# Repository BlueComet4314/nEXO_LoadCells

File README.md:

# nEXO_LoadCells
Schematics for LoadCell Level Sensor work

## Schematic of PT100 circuit: 

## PCB Layout Vers. 02:

Parts:

| L0C | Part - Desc. | Digikey PIN |
| -- | -- | -- |
|C1| CAP_THT-0.1uF - 2.50mm | 2368-89410-ND |
|C2| CAP_SMD-47pF - 1.4mm | 490-6129-2-ND |
|C3| CAP_SMD-22pF - 1.4mm | 490-1253-2-ND |
|C6| CAP_SMD-68pF - 1.4mm | 490-11338-2-ND |
|J1| Conn-01x02_Male - 2.54mm | 77311-402-02LF-ND |
|J2| Conn-01x04_Female -2.54mm | 609-3920-ND |
|J3/J5| Load Cell Amp - HX711 | 1568-1436-ND |
| J4 & J6-10 | Conn header Vert-4POS - 2.54 mm | WM4826-ND|
|MCU1| Teensy 4.1 | 1568-DEV-16771-ND |
|P2| Arduino socket strip - Analog 01x08| 732-2859-ND |
|P4| Arduino socket strip - Power 01x08 | 732-2859-ND |
|P5| Arduino socket strip - PWM-01x10| S7008-ND |
|P6| Arduino socket strip - PWM-01x08 | 732-2859-ND |
|P8-P13| Arduino CONN 01X01 | SAM1122-01-ND |
|R2-R4| Resistor_SMD-10K | 2997-CR20103JTR-ND |
|R5| Resistor_SMD - 82k | 2997-CR20823JTR-ND |
|R6| Resistor_SMD - 39k | 2997-CR20393JTR-ND |
|Teensy_Ethernet1| Teensy Ethernet 1P | 1278-1052-ND |
|U1| MSOP-10P| 505-AD7151BRMZ-ND |

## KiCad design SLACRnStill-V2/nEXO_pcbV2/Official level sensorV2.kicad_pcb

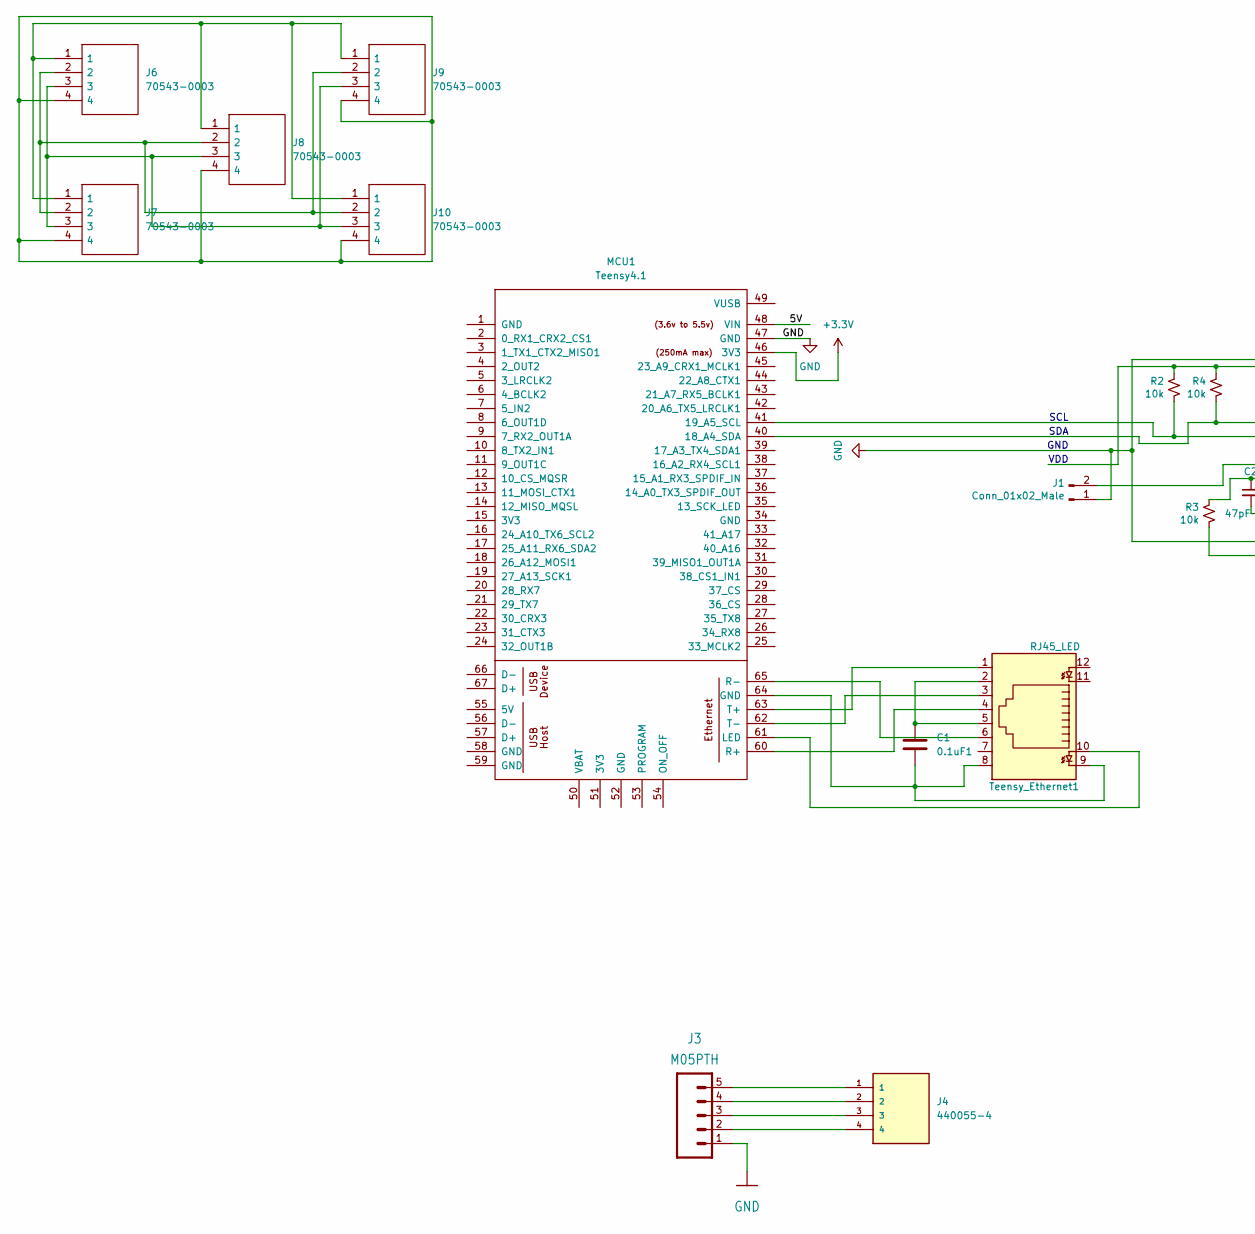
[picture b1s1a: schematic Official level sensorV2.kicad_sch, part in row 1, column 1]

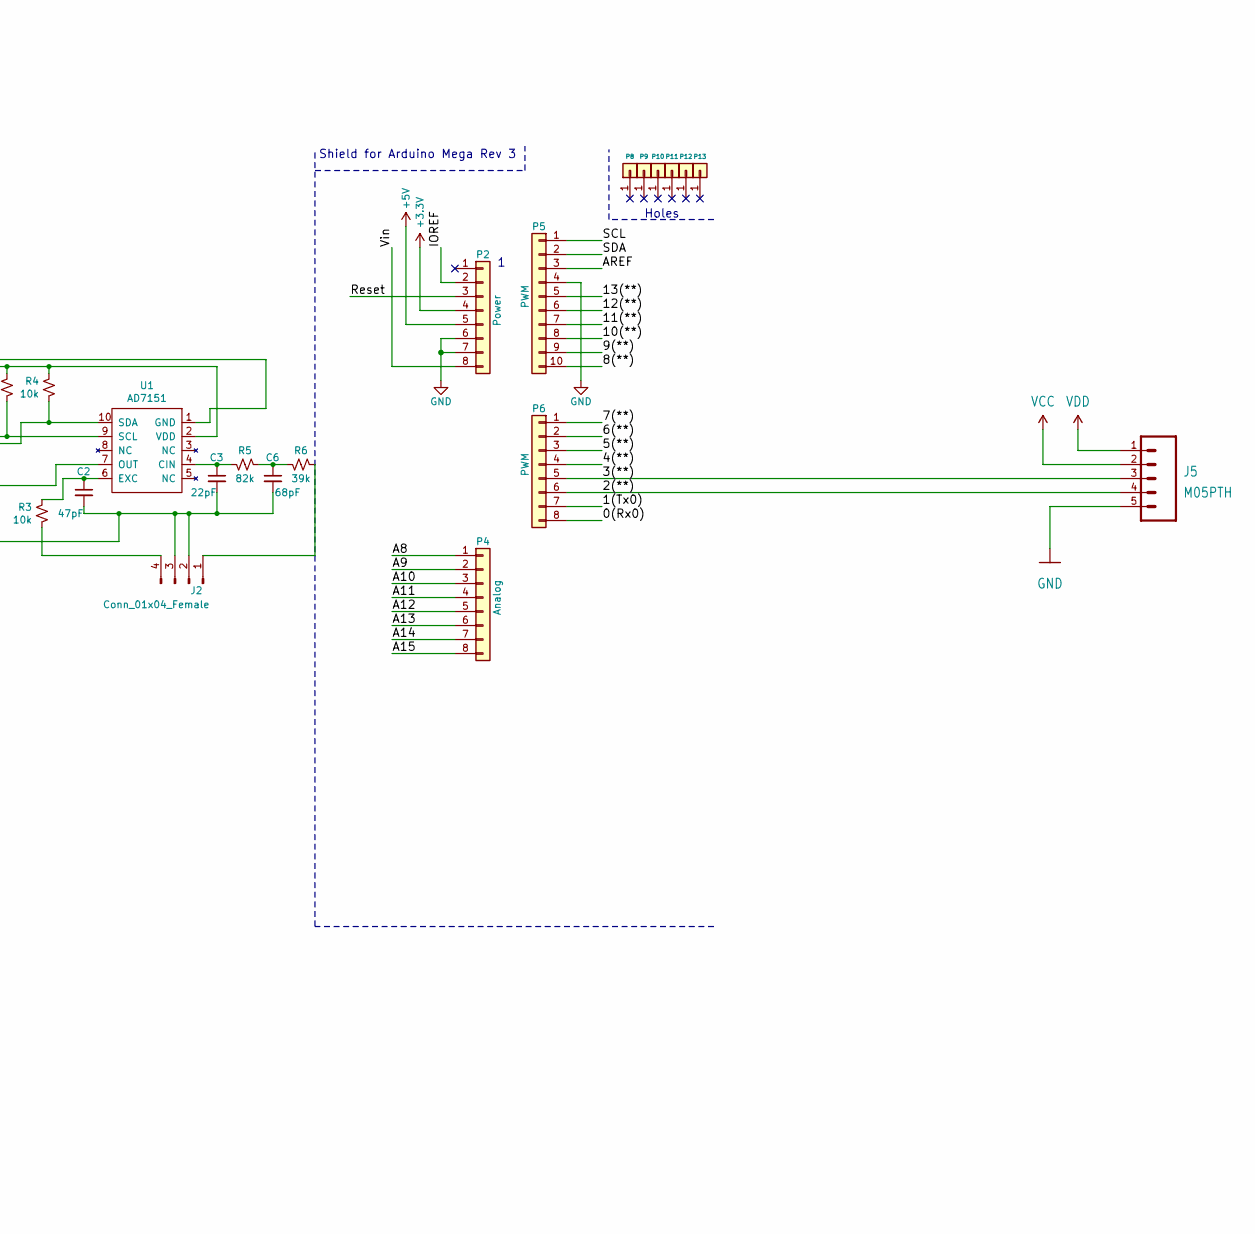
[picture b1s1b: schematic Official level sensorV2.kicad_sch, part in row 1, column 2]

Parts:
C1: 0.1uF1; C_Disc_D3.0mm_W1.6mm_P2.50mm
C2: 47pF; C_0805_2012Metric_Pad1.15x1.40mm_HandSolder
C3: 22pF; C_0805_2012Metric_Pad1.15x1.40mm_HandSolder
C6: 68pF; C_0805_2012Metric_Pad1.15x1.40mm_HandSolder
J1: Conn_01x02_Male; PinHeader_1x02_P2.54mm_Vertical
J2: Conn_01x04_Female; Amphenol Anytech YO 3.81mm 4p; DigikeyPN 609-3920-ND
J3, J5: M05PTH; 1X05
J4: 440055-4; SHDR4W97P0X254_1X4_1271X660X1143P
J6, J7, J8, J9, J10: 70543-0003; SHDR4W97P0X254_1X4_1271X660X1143P; Mouser Part Number 538-70543-0003
MCU1: Teensy4.1; Teensy41
P2: Power; Socket_Strip_Arduino_1x08
P4: Analog; Socket_Strip_Arduino_1x08
P5: PWM; Socket_Strip_Arduino_1x10
P6: PWM; Socket_Strip_Arduino_1x08
P8, P9, P10, P11, P12, P13: CONN_01X01; Arduino_1pin
R2, R3, R4: 10k; R_0805_2012Metric_Pad1.15x1.40mm_HandSolder
R5: 82k; R_0805_2012Metric_Pad1.15x1.40mm_HandSolder
R6: 39k; R_0805_2012Metric_Pad1.15x1.40mm_HandSolder
Teensy_Ethernet1: RJ45_LED; RJ45_Cetus_J1B1211CCD_Horizontal
U1: AD7151; MSOP-10_3x3mm_P0.5mm; DigikeyPN AD7151BRMZ-ND

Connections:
+3V3: MCU1.46 (3V3), P2.4
+5V: P2.5
/0(Rx0): P6.8
/1(Tx0): P6.7
/2(**): J5.4, P6.6
/3(**): J5.3, P6.5
/4(**): P6.4
/5(**): P6.3
/5V: MCU1.48 (VIN)
/6(**): P6.2
/7(**): P6.1
/8(**): P5.10
/9(**): P5.9
/10(**): P5.8
/11(**): P5.7
/12(**): P5.6
/13(**): P5.5
/A8: P4.1
/A9: P4.2
/A10: P4.3
/A11: P4.4
/A12: P4.5
/A13: P4.6
/A14: P4.7
/A15: P4.8
/AREF: P5.3
/IOREF: P2.2
/Reset: P2.3
/SCL: P5.1
/SDA: P5.2
/Vin: P2.8
GND: C2.2, C3.2, C6.2, J1.1, J2.2, J2.3, J3.1, J5.5, MCU1.47 (GND), P2.6, P2.7, P5.4, U1.1 (GND)
unnamed: C1.1, Teensy_Ethernet1.2, Teensy_Ethernet1.5
unnamed: C1.2, MCU1.64 (GND), Teensy_Ethernet1.8, Teensy_Ethernet1.9
unnamed: C2.1, R3.1, U1.6 (EXC)
unnamed: C3.1, R5.1, U1.4 (CIN)
unnamed: C6.1, R5.2, R6.1
unnamed: J1.2, U1.7 (OUT)
unnamed: J2.1, R6.2
unnamed: J2.4, R3.2
unnamed: J3.2, J4.4
unnamed: J3.3, J4.3
unnamed: J3.4, J4.2
unnamed: J3.5, J4.1
unnamed: J6.1, J7.1, J8.1, J9.1, J10.1
unnamed: J6.2, J7.2, J8.2, J9.2, J10.2
unnamed: J6.3, J7.3, J8.3, J9.3, J10.3
unnamed: J6.4, J7.4, J8.4, J9.4, J10.4
unnamed: MCU1.40 (18_A4_SDA), R4.2, U1.10 (SDA)
unnamed: MCU1.41 (19_A5_SCL), R2.2, U1.9 (SCL)
unnamed: MCU1.60 (R+), Teensy_Ethernet1.4
unnamed: MCU1.61 (LED), Teensy_Ethernet1.10
unnamed: MCU1.62 (T-), Teensy_Ethernet1.3
unnamed: MCU1.63 (T+), Teensy_Ethernet1.1
unnamed: MCU1.65 (R-), Teensy_Ethernet1.6
unnamed: R2.1, R4.1, U1.2 (VDD)
VCC: J5.2
VDD: J5.1

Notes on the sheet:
SCL
SDA
GND
Holes
VDD
Shield for Arduino Mega Rev 3

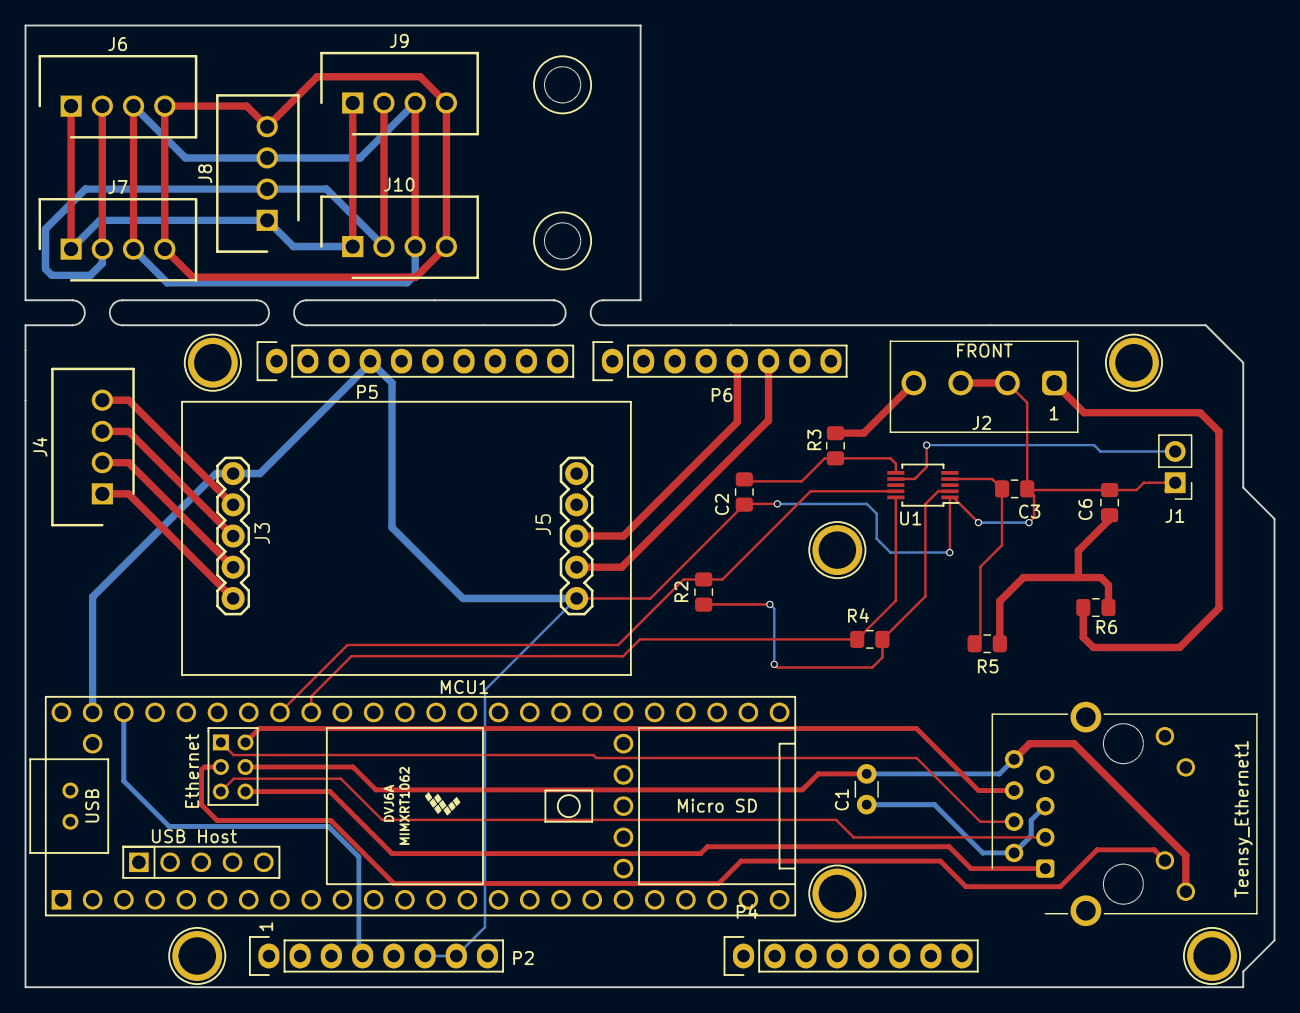
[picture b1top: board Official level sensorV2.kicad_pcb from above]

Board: 2 copper layers, 101.6 x 78.2 mm, 32 parts (0 on the bottom side), 28 nets.

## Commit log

2022-07-13 I adressed issue #1
